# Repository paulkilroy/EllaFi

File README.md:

# EllaFi

Coin-operated WiFi hotspot portal for ESP32, built for TP-Link Omada controller networks. Clients insert physical coins to purchase internet access — the ESP32 handles coin counting, session management, pause/resume, and communicates with the Omada controller to grant and revoke access.

## Flash & Provision

**[→ Open the EllaFi Provisioner](https://paulkilroy.github.io/EllaFi/flasher.html)** — browser-based tool (Chrome/Edge) to flash firmware and configure a new node over USB. No Python or esptool install required.

---

## Features

- **Coin-operated access** — physical coin acceptor triggers ISR; 10s window accumulates coins before finalizing
- **Real-time UI** — captive portal page communicates via WebSocket; session timer, progress bar, and coin insert countdown update live
- **Pause & resume** — clients can pause their session and resume later; remaining time is saved to flash
- **Multi-node support** — master/slave architecture over UDP broadcast; slave nodes accept coins and report to the master via LAN
- **Session reconstruction** — on reboot, the ESP32 queries the Omada controller to restore active sessions without requiring re-authentication
- **Error handling** — structured error subtypes (`no_session`, `refundable`) with permanent UI popups for unrecoverable states
- **Captive portal** — integrates with Omada's External Portal Server auth flow; works with EAP603 and similar APs

---

## Hardware

- ESP32 (tested on ESP32-S3 DevKitC-1)
- Coin acceptor wired to GPIO4 via PC817 optocoupler (GPIO0 / BOOT button also works for testing)
- TP-Link Omada controller with hotspot operator account
- Omada EAP access points on the same LAN

### Coin Acceptor Wiring

Coin acceptor pinout reference: https://www.cable-tester.com/coin-acceptor-connector-pin-out/

```
                    P6KE6.8A (TVS)
Coin acceptor SIG ──┬── (across signal to GND) ── GND
                    │
                    └── PC817 PIN2 (Cathode)

3.3V ── 220Ω ─────── PC817 PIN1 (Anode)
                     PC817 PIN3 (Emitter) ──── GND
                     PC817 PIN4 (Collector) ── 10kΩ ──── GPIO4

Coin acceptor GND ──────────────────────────────────── GND (shared)
```

- **PC817** — optocoupler for galvanic isolation between coin acceptor and 3.3V ESP32
- **220Ω** (input side, R2) — limits PC817 LED current from 3.3V; (3.3V − 1.2V Vf) / 220Ω ≈ 9.5mA
- **10kΩ** (output side, R1) — series resistor between PC817 collector and GPIO4; GPIO4 uses ESP32 internal pull-up (INPUT_PULLUP). When PC817 conducts, GPIO4 is pulled low through R1; when off, internal pull-up holds GPIO4 high
- **P6KE6.8A TVS diode** — clamps piezo lighter spikes (10-20kV) to GND before they reach the PC817; bidirectional, wired across signal line to GND; rated 600W peak pulse, effectively unlimited lifetime at 1 spike/second. With 3.3V drive, the signal line idles at ~2.1V — well below the 6.8V clamp — so TVS only fires on actual spikes, not at idle
- **Anti-pitik (software)** — ISR triggers on CHANGE (both edges) on both GPIO4 (coin slot) and GPIO0 (boot button); measures pulse width, rejects anything under 5ms. Piezo spikes attenuated by PC817 to ~5µs on GPIO4, and couple electromagnetically into GPIO0 — both paths filtered by the same threshold

### PCB Wiring (Full Circuit)

Within each net, order doesn't matter — wire items in whatever sequence is convenient for your layout.

**+12V net**
- J3 pin 1 (barrel jack +)
- C1 pin 1 (input cap +)
- U3 pin 1 (LM2596 VIN)
- J1 pin 1 (coin acceptor power)
- J2 pin 1 (LED ring + power)

**GND net**
- J3 pin 2 (barrel jack GND)
- C1 pin 2 (input cap −)
- U3 pin 3 (LM2596 GND)
- U3 pin 5 (LM2596 ON/OFF — tie to GND = always on)
- D2 pin 2 (freewheeling diode anode)
- C2 pin 2 (output cap −)
- Q1 pin 3 (MOSFET source)
- U1 pin 3 (PC817 emitter)
- U2 pins 22, 23, 24, 44 (ESP32 GND)
- D1 pin 1 (TVS anode — system GND directly, not switched)

** More documentation on the LM2596 here: https://www.ti.com/lit/ds/symlink/lm2596.pdf
**Switching node** (short wires — keep these close together)
- U3 pin 2 (LM2596 OUT)
- D2 pin 1 (freewheeling diode cathode)
- L1 pin 1

**+5V net**
- L1 pin 2 (inductor output)
- C2 pin 1 (output cap +)
- U3 pin 4 (LM2596 FB)
- U2 pin 21 (ESP32 5V)

**+3.3V net**
- U2 pin 2 (ESP32 3V3 output)
- R2 pin 1 (PC817 LED current limiter, 220Ω)

**Switched GND node** — controlled by Q1 (MOSFET); HIGH on GPIO14 = coin slot on
- Q1 pin 2 (MOSFET drain)
- J1 pin 3 (coin acceptor GND)
- J2 pin 2 (activate signal — hardwired to pin 3; always on when switched power is on)
- J2 pin 3 (LED ring GND −)

J2 is a 3-pin screw terminal (2.54mm or 5.08mm pitch). 2-wire LED rings: use pins 1 and 3. 3-wire LED rings (with activate signal): use all 3 pins — pins 2 and 3 are both on switched GND, so activate is always asserted.

**Coin signal node**
- J1 pin 2 (coin acceptor open-collector output — LOW = coin pulse)
- U1 pin 2 (PC817 LED cathode)
- D1 pin 2 (TVS cathode — clamps spikes; orient banded end toward this node)

**R2 → PC817 LED**
- R2 pin 2
- U1 pin 1 (PC817 LED anode)

**PC817 output → ESP32 coin pulse (GPIO4)** — series path, not a single net
- U1 pin 4 (PC817 collector) → R1 (10kΩ) → U2 pin 4 (GPIO4, COINSLOT_PIN)
- R1 limits collector current; GPIO4 pulled high by ESP32 internal pull-up

**Q1 gate — coin slot enable (GPIO14)**
- Q1 pin 1 (MOSFET gate)
- U2 pin 20 (GPIO14, COINSLOT_POWER_PIN)

J1 pin 4 — NC (leave unconnected)

---

## Bill of Materials (DigiKey)

| Ref          | Description                                          | DigiKey #              | Qty | Confidence | Verify |
|--------------|------------------------------------------------------|------------------------|-----|------------|--------|
| R1           | 10kΩ 0.25W axial THT (DIN0207)                      | `MF0207FRE52-10K-ND`   | 1   | 90% | DigiKey confirmed body 6.3mm ✓, dia 2.4mm (spec 2.5mm) — check fits through pads; lead pitch not confirmed |
| R2, R4, R5   | 220Ω 0.25W axial THT                                | `220QBK-ND`            | 3   | 90% | Same series as R1 — same caveats |
| R3           | 330Ω 0.25W axial THT                                | `330QBK-ND`            | 1   | 90% | Same series as R1 — same caveats |
| C1, C2       | 100uF 25V radial electrolytic 8mm/3.5mm             | `493-14973-ND`         | 2   | 99% | DigiKey confirmed 8.0mm dia ✓, 3.5mm pitch ✓ |
| D1           | P6KE6.8A TVS diode DO-15                            | `P6KE6.8ALFCT-ND`      | 1   | 90% | Footprint needs P10.16mm lead pitch — confirm on DigiKey "Lead Spacing" spec |
| D2           | 1N5822 Schottky diode DO-201AD                      | `1N5822-E3/54GICT-ND`  | 1   | 90% | Footprint needs P15.24mm lead pitch — confirm on DigiKey "Lead Spacing" spec |
| D3           | 3mm right-angle LED red                             | `754-1298-ND`          | 1   | 90% | Footprint is `O1.27mm_Z2.0mm` — confirm horizontal offset and height on DigiKey dimensional drawing |
| D4           | 3mm right-angle LED yellow                          | `754-1300-ND`          | 1   | 90% | Same series as D3 — same caveats |
| D5           | 3mm right-angle LED green                           | `754-1297-ND`          | 1   | 90% | Same series as D3 — same caveats |
| Q1           | IRF540N N-channel MOSFET TO-220-3                   | `IRF540NPBF-ND`        | 1   | 90% | Footprint is vertical TO-220-3 — confirm part is vertical mount not tab-down horizontal |
| SW1          | OS102011MS2QN1 SPDT slide switch                    | `CKN9565-ND`           | 1   | 99% | Exact C&K part number — KiCad footprint named after this exact part |
| U1           | FOD817 optocoupler DIP-4 (PC817 compatible)         | `FOD817-ND`            | 1   | 95% | Standard DIP-4 7.62mm row spacing — confirm FOD817 matches PC817 pin layout |
| U3           | LM2596T-5.0 buck regulator TO-220-5                 | `LM2596T-5.0/NOPB-ND`  | 1   | 90% | TO-220-5 stagger confirmed; 1.70mm lead pitch × 2 = 3.4mm span matches `P3.4x3.7mm_StaggerEven` ✓ |
| L1           | 100uH radial inductor 9.5mm dia / 5mm pitch         | `732-3081-ND`          | 1   | 90% | DigiKey confirmed 9.5mm dia ✓; 5mm pitch from Würth series spec, not directly on DigiKey page |
| J1           | 1×4 female socket 2.54mm                           | `S7037-ND`             | 1   | 95% | Standard 2.54mm pitch — Sullins exact part, KiCad footprint named to spec |
| J2           | 3-pos terminal block 5.08mm pitch                  | `277-1976-ND`          | 1   | 95% | Phoenix Contact exact part — 5.08mm pitch confirmed |
| J3           | CUI PJ-002AH barrel jack 2.1mm ID / 5.5mm OD       | `CP-002AH-ND`          | 1   | 75% | Center-to-sleeve 3.0mm confirmed ✓; mounting tab offset ~3.0mm but KiCad footprint uses 3.5mm — tab holes may not align, verify before routing |
| J4, J5       | 1×22 female socket 2.54mm (ESP32 DevKitC-1)        | `S7055-ND`             | 2   | 95% | Standard 2.54mm pitch — Sullins exact part |

---

## How It Works

1. Client connects to WiFi → Omada redirects to captive portal
2. Portal page opens via WebSocket; ESP32 pushes session status
3. Client clicks **Insert Coins** → coin insert mode activates
4. Physical coins trigger GPIO pulses (debounced ISR)
5. After 10s of inactivity, ESP32 calls Omada API to authenticate or extend the session
6. Client is redirected to the internet; session timer counts down live
7. Client can **pause** (disconnects from Omada, saves remaining time) and **resume** (re-authenticates with saved duration)

---

## Configuration

Copy `data/config.sample.json` to `data/config.json` and fill in:

```json
{
  "wifi_ssid": "YourWiFiNetwork",          // SSID of the WiFi network the ESP32 joins
  "wifi_password": "...",                  // WiFi password
  "omada_url": "https://...",              // Omada controller URL (Settings → Controller → URL)
  "omada_controller_id": "...",            // Omada controller ID (visible in the controller URL path)
  "omada_operator_username": "...",        // Hotspot operator account (Hotspot → Operator Accounts)
  "omada_operator_password": "...",        //   ↑ same account
  "omada_username": "...",                 // Omada admin account (Settings → Administrators)
  "omada_password": "...",                 //   ↑ same account
  "master_mac": "AA:BB:CC:DD:EE:FF",      // WiFi MAC of the master ESP32 node (printed on boot)
  "network_key": 12345678                  // Shared secret for UDP broadcast between nodes (any number)
}
```

`data/config.json` is gitignored and never committed.

---

## Build & Flash

**Easiest:** use the [browser-based provisioner](https://paulkilroy.github.io/EllaFi/flasher.html) — no tools to install.

**From source** — requires [PlatformIO](https://platformio.org/):

```bash
# Build and flash firmware
pio run --target upload

# Upload web files (captive portal HTML) to LittleFS
pio run --target uploadfs

# Monitor serial output
pio device monitor
```

Tag a release to trigger a GitHub Actions build and publish firmware binaries:

```bash
git tag v1.0.0 && git push --tags
```

---

## Testing

See [test/TESTING.md](test/TESTING.md) for full details.

```bash
# Run all automated tests against a live ESP32
python3 test/run_all_tests.py --host <ESP32_IP>

# UI state walkthrough (paste into browser console on data/index.html)
# Use ← → arrow keys to step through all UI states
test/ui_state_test.js
```

---

## Project Structure

```
src/
  main.cpp        # Firmware: captive portal, coin handling, WebSocket, session logic
  omada.cpp/.h    # Omada controller API client (auth, extend, disconnect, session cache)
  network.cpp/.h  # UDP broadcast, master/slave role detection
data/
  index.html      # Captive portal UI (single-file, no dependencies)
  config.sample.json
test/
  mock_omada.py             # Local Omada controller mock for testing
  stress_test_happy_path.py # Full coin insert → auth flow
  stress_test_race_conditions.py
  stress_test_chaos.py
  ui_state_test.js          # Browser console UI walkthrough
```

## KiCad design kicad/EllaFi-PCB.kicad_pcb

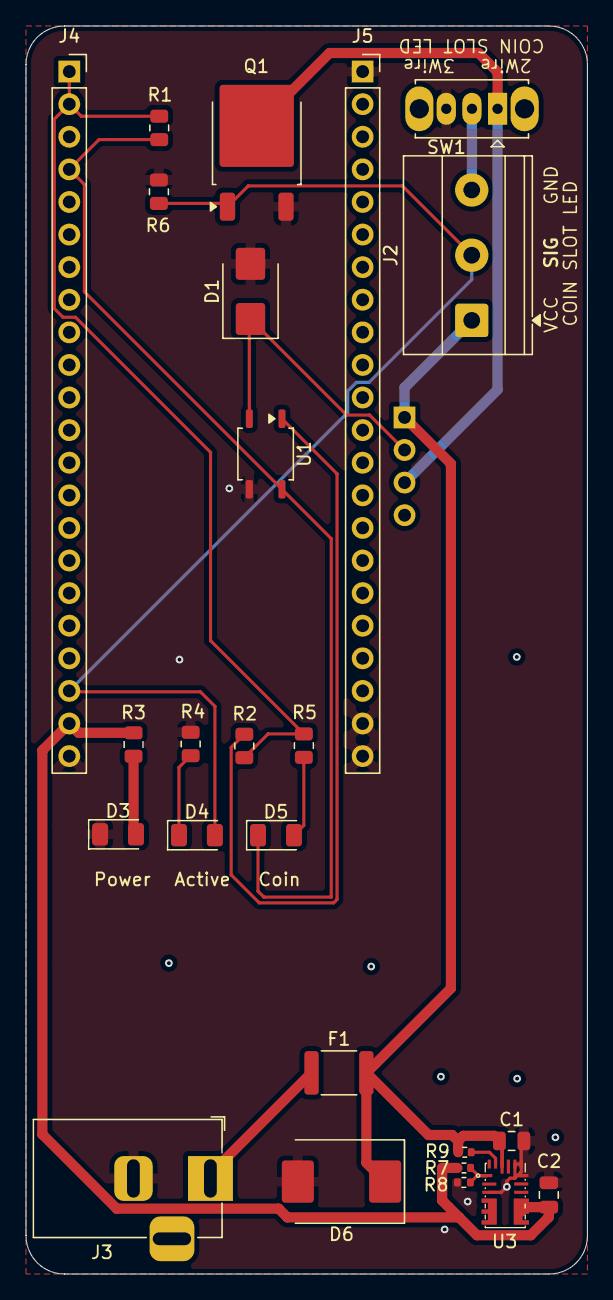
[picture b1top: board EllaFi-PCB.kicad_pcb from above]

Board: 2 copper layers, 43.8 x 97.2 mm, 26 parts (1 on the bottom side), 16 nets.

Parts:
C1: 10 µF; C_0805_2012Metric
C2: 22 µF; C_0805_2012Metric
D1: P6SMB6.8A; D_SMB
D3: LED-RED; LED_1206_3216Metric
D4: LED-YELLOW; LED_1206_3216Metric
D5: LED-GREEN; LED_1206_3216Metric
D6: 1.5SMC18A; D_SMC
F1: MINISMDC150F/16-2; Fuse_1812_4532Metric
J1: Conn_01x04_Socket; PinSocket_1x04_P2.54mm_Vertical
J2: Conn_01x03; TerminalBlock_Phoenix_MKDS-1,5-3-5.08_1x03_P5.08mm_Horizont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
J3: PJ-002AH; BarrelJack_Horizontal
J4, J5: Conn_01x22_Socket; PinSocket_1x22_P2.54mm_Vertical
Q1: AOD4184A; TO-252-2
R1: 2.2k; R_0805_2012Metric
R2, R4: 220; R_0805_2012Metric
R3: 330; R_0805_2012Metric
R5: 1k; R_0805_2012Metric
R6: 10k; R_0805_2012Metric
R7, R9: 100 kΩ; R_0402_1005Metric
R8: 19.1 kΩ; R_0402_1005Metric
SW1: OS102011MS2QN1; SW_Slide_SPDT_Straight_CK_OS102011MS2Q
U1: FOD817S; SOP-4_3.8x4.1mm_P2.54mm
U3: MPM3620AGQV-Z; QFN-20_L5.0-W3.0-TL-MPM3630GQV-Z

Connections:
+12V: F1.1, J3.1
/3V3: J4.1, J4.2, R1.2, R2.1, R5.1
/5V: C2.1, J4.21, R3.1, R7.1, U3.9 (OUT)
/GPIO4: D5.1 (K), J4.4, R1.1, U1.4
/GPIO14: D4.2 (A), J2.2, J4.20, Q1.1 (G), R6.2
GND: C1.2, C2.2, D1.2 (A2), D3.1 (K), D6.2 (A2), J3.2, J4.22, J5.1, J5.21, J5.22, Q1.3 (S), R4.2, R6.1, R8.2, SW1.3 (C), U1.3, U3.3 (AGND), U3.12 (PGND), U3.13 (PGND), U3.14 (PGND)
unnamed: D1.1 (A1), J1.2, U1.2
unnamed: D3.2 (A), R3.2
unnamed: D4.1 (K), R4.1
unnamed: D5.2 (A), R5.2
unnamed: C1.1, D6.1 (A1), F1.2, J1.1, J2.1, R9.1, U3.16 (IN)
unnamed: J1.3, Q1.2 (D), SW1.1 (A)
unnamed: J2.3, SW1.2 (B)
unnamed: R2.2, U1.1
unnamed: R9.2, U3.17 (EN)
unnamed: R7.2, R8.1, U3.1 (FB)

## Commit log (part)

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2026-03-10 Remove DS_Store, Claude settings, pycache; update gitignore
2026-03-15 refactoed the interprocess communication
2026-03-16 cleaned up logging, shrunk images and change led startup pattern
2026-03-16 cleaned up warnings
2026-03-19 removed old debugging
2026-03-20 code cleanups
2026-05-02 lot of fixes
2026-05-07 cleanups and fixes
2026-05-10 connection and timeout fixes
2026-05-27 old sound message
2026-05-27 Multi-node OTA cascade, embedded static files, admin log page
    OTA cascade (master → slave auto-update):
    - UDP heartbeat every 15s; master triggers OTA when slave build < own build
    - Fix: always read full packet body before early returns in networkLoop()
    (partial HeartbeatBody reads left 63 stale bytes, permanently stalling parsePacket)
    - Deauth before esp_restart() in slaveOtaTask prevents UDP-deaf on reconnect
    - Stale-bytes diagnostic: logs WARN if bytes remain in socket before parsePacket
2026-05-31 Update firmware binaries [skip ci]
2026-05-31 Fix Transport undefined: switch to ES module import for esptool-js
2026-05-31 Fix Buffer undefined: import esptool-js via esm.sh for browser polyfills
2026-05-31 Fix LittleFS erase: write 0x00 not 0xFF to corrupt superblock
2026-05-31 Fresh Install: use eraseAll to wipe chip instead of partial LittleFS erase
